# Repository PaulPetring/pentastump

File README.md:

# pentastump
KiCad USB PCB with AtTiny85 and 7805

# PCB

#Scheme

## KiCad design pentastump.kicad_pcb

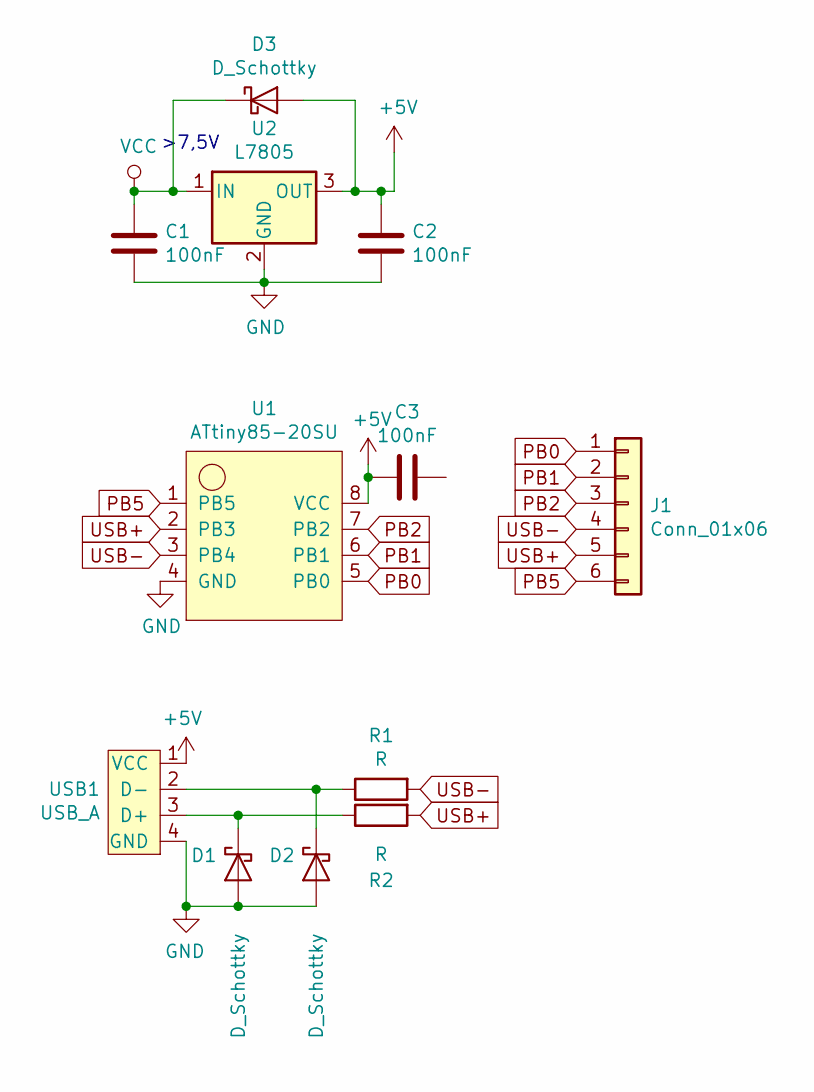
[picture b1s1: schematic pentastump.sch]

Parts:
C1, C2, C3: 100nF; C_0805_2012Metric
D1, D2, D3: D_Schottky; D_0805_2012Metric
J1: Conn_01x06; PinHeader_1x06_P2.54mm_Vertical
R1, R2: R; R_0805_2012Metric
U1: ATtiny85-20SU; DIP-8_W7.62mm
U2: L7805; TO-220-3_Vertical
USB1: USB_A; USB_A_PCB

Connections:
+5V: C2.1, C3.2, D3.2 (A), U1.8 (VCC), U2.3 (OUT), USB1.1 (VCC)
GND: C1.2, C2.2, D1.2 (A), D2.2 (A), U1.4 (GND), U2.2 (GND), USB1.4 (GND)
unnamed: D1.1 (K), R2.1, USB1.3 (D+)
unnamed: D2.1 (K), R1.1, USB1.2 (D-)
PB0: J1.1, U1.5 (PB0)
PB1: J1.2, U1.6 (PB1)
PB2: J1.3, U1.7 (PB2)
PB5: J1.6, U1.1 (PB5)
USB+: J1.5, R2.2, U1.2 (PB3)
USB-: J1.4, R1.2, U1.3 (PB4)
VCC: C1.1, D3.1 (K), U2.1 (IN)

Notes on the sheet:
>7,5V

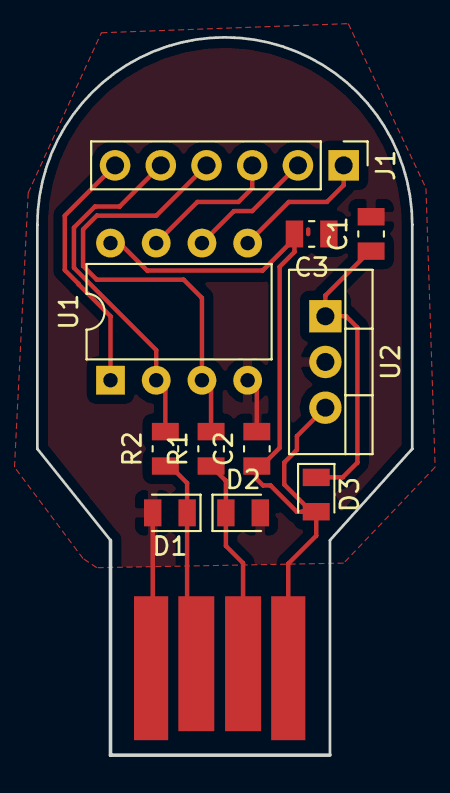
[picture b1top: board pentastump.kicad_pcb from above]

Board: 2 copper layers, 20.8 x 39.9 mm, 12 parts (0 on the bottom side), 11 nets.
